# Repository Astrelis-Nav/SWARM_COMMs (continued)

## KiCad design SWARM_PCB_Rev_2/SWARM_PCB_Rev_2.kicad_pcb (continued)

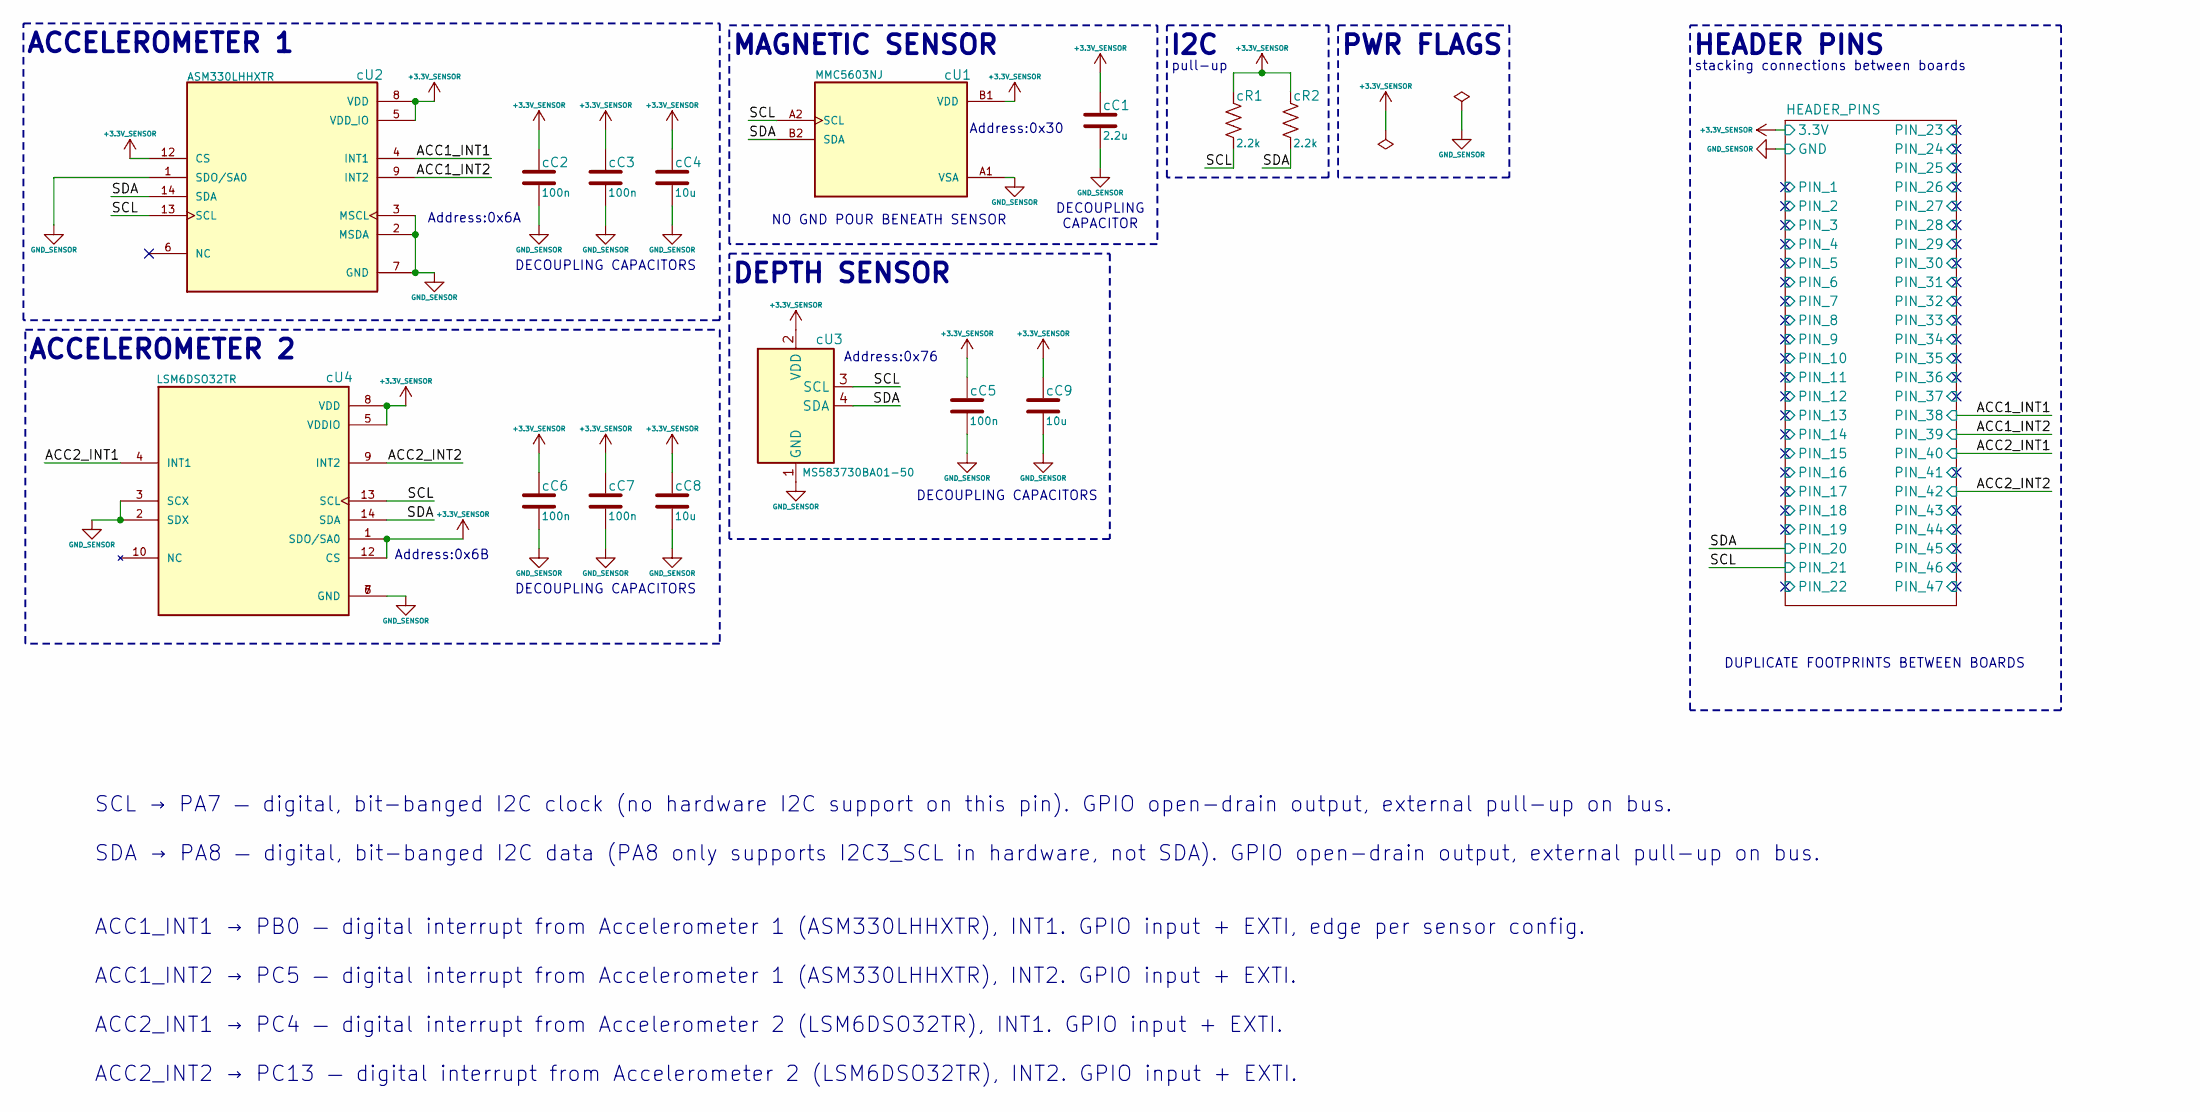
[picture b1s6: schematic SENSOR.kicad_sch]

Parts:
cC1: 2.2u; C_0603_1608Metric; MPN GRM188R60J225KE15D
cC2, cC3, cC5, cC6, cC7: 100n; C_0603_1608Metric; MPN GRM188R71C104KA01D
cC4, cC8, cC9: 10u; C_0603_1608Metric; MPN GRM188R60J106ME47D
cR1, cR2: 2.2k; R_0603_1608Metric; MPN RC0603FR-072K2L
cU1: MMC5603NJ; XDCR_MMC5603NJ; PARTREV B
cU2: ASM330LHHXTR; XDCR_ASM330LHHXTR; PARTREV 8
cU3: MS583730BA01-50; TE_MS5837-xxBA; MPN MS583730BA01-50
cU4: LSM6DSO32TR; XDCR_LSM6DSO32TR; PARTREV 1

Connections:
+3.3V_SENSOR: cC1.2, cC2.2, cC3.2, cC4.2, cC5.2, cC6.2, cC7.2, cC8.2, cC9.2, cR1.2, cR2.2, cU1.B1 (VDD), cU2.5 (VDD_IO), cU2.8 (VDD), cU2.12 (CS), cU3.2 (VDD), cU4.1 (SDO/SA0), cU4.5 (VDDIO), cU4.8 (VDD), cU4.12 (CS); also elsewhere on the board
/SENSOR/ACC1_INT1: cU2.4 (INT1); also elsewhere on the board
/SENSOR/ACC1_INT2: cU2.9 (INT2); also elsewhere on the board
/SENSOR/ACC2_INT1: cU4.4 (INT1); also elsewhere on the board
/SENSOR/ACC2_INT2: cU4.9 (INT2); also elsewhere on the board
/SENSOR/SCL: cR1.1, cU1.A2 (SCL), cU2.13 (SCL), cU3.3 (SCL), cU4.13 (SCL); also elsewhere on the board
/SENSOR/SDA: cR2.1, cU1.B2 (SDA), cU2.14 (SDA), cU3.4 (SDA), cU4.14 (SDA); also elsewhere on the board
GND_SENSOR: cC1.1, cC2.1, cC3.1, cC4.1, cC5.1, cC6.1, cC7.1, cC8.1, cC9.1, cU1.A1 (VSA), cU2.1 (SDO/SA0), cU2.2 (MSDA), cU2.3 (MSCL), cU2.7 (GND), cU3.1 (GND), cU4.2 (SDX), cU4.3 (SCX), cU4.6 (GND), cU4.7 (GND); also elsewhere on the board

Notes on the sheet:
Address:0x76
DECOUPLING CAPACITOR
DEPTH SENSOR
stacking connections between boards
MAGNETIC SENSOR
Address:0x6A
SCL → PA7 — digital, bit-banged I2C clock (no hardware I2C support on this pin). GPIO open-drain output, external pull-up on bus. SDA → PA8 — digital, bit-banged I2C data (PA8 only supports I2C3_SCL in hardware, not SDA). GPIO open-drain output, external pull-up on bus. ACC1_INT1 → PB0 — digital in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
DUPLICATE FOOTPRINTS BETWEEN BOARDS
DECOUPLING CAPACITORS
pull-up
Address:0x6B
ACCELEROMETER 2
Address:0x30
I2C
NO GND POUR BENEATH SENSOR
DECOUPLING CAPACITORS
PWR FLAGS
ACCELEROMETER 1
HEADER PINS

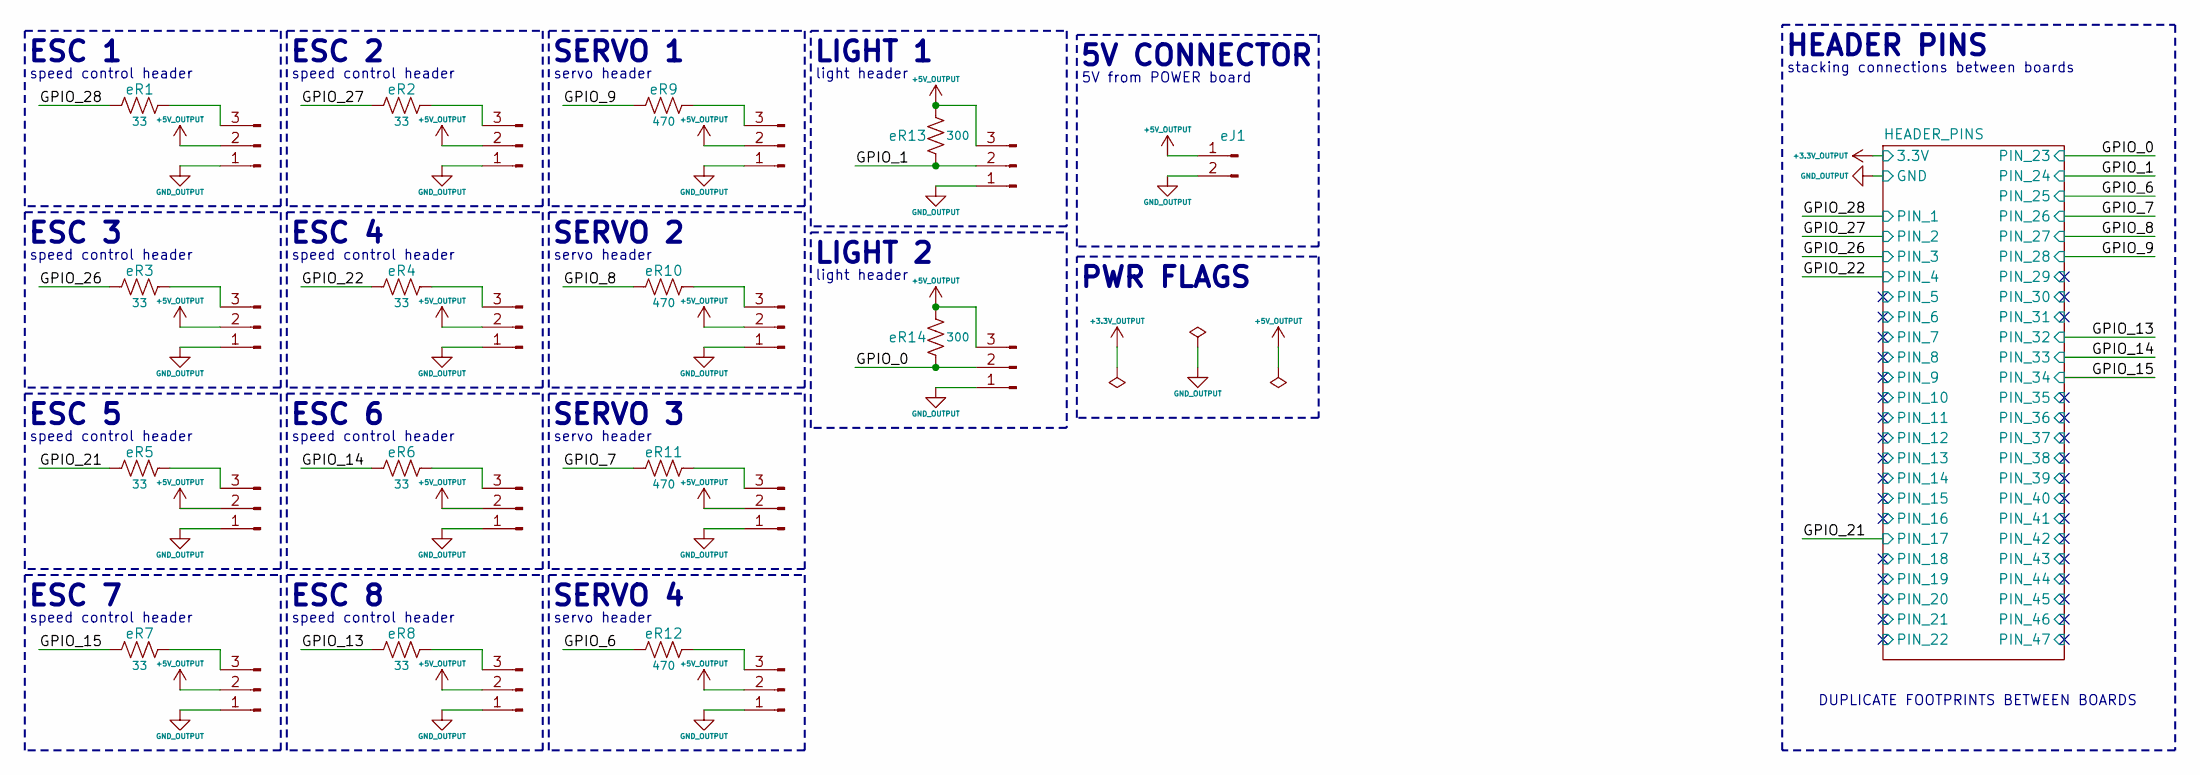
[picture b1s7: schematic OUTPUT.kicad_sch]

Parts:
OUT_1, OUT_2, OUT_3, OUT_4, OUT_5, OUT_6, OUT_7, OUT_8, OUT_9, OUT_10, OUT_11, OUT_12, OUT_13, OUT_14: Conn_01x03_Pin; PinHeader_1x03_P2.54mm_Vertical
eJ1: Conn_01x02_Pin; JST_PH_B2B-PH-SM4-TB_1x02-1MP_P2.00mm_Vertical
eR1, eR2, eR3, eR4, eR5, eR6, eR7, eR8: 33; R_0603_1608Metric
eR9, eR10, eR11, eR12: 470; R_0603_1608Metric
eR13, eR14: 300; R_0603_1608Metric

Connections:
+5V_OUTPUT: OUT_1.2, OUT_2.2, OUT_3.2, OUT_4.2, OUT_5.2, OUT_6.2, OUT_7.2, OUT_8.2, OUT_9.2, OUT_10.2, OUT_11.2, OUT_12.2, OUT_13.3, OUT_14.3, eJ1.1, eR13.2, eR14.2
/OUTPUT/GPIO_0: OUT_14.2, eR14.1; also elsewhere on the board
/OUTPUT/GPIO_1: OUT_13.2, eR13.1; also elsewhere on the board
/OUTPUT/GPIO_6: eR12.1; also elsewhere on the board
/OUTPUT/GPIO_7: eR11.1; also elsewhere on the board
/OUTPUT/GPIO_8: eR10.1; also elsewhere on the board
/OUTPUT/GPIO_9: eR9.1; also elsewhere on the board
/OUTPUT/GPIO_13: eR8.1; also elsewhere on the board
/OUTPUT/GPIO_14: eR6.1; also elsewhere on the board
/OUTPUT/GPIO_15: eR7.1; also elsewhere on the board
/OUTPUT/GPIO_21: eR5.1; also elsewhere on the board
/OUTPUT/GPIO_22: eR4.1; also elsewhere on the board
/OUTPUT/GPIO_26: eR3.1; also elsewhere on the board
/OUTPUT/GPIO_27: eR2.1; also elsewhere on the board
/OUTPUT/GPIO_28: eR1.1; also elsewhere on the board
GND_OUTPUT: OUT_1.1, OUT_2.1, OUT_3.1, OUT_4.1, OUT_5.1, OUT_6.1, OUT_7.1, OUT_8.1, OUT_9.1, OUT_10.1, OUT_11.1, OUT_12.1, OUT_13.1, OUT_14.1, eJ1.2; also elsewhere on the board
unnamed: OUT_1.3, eR1.2
unnamed: OUT_2.3, eR2.2
unnamed: OUT_3.3, eR3.2
unnamed: OUT_4.3, eR4.2
unnamed: OUT_5.3, eR5.2
unnamed: OUT_6.3, eR6.2
unnamed: OUT_7.3, eR7.2
unnamed: OUT_8.3, eR8.2
unnamed: OUT_9.3, eR9.2
unnamed: OUT_10.3, eR10.2
unnamed: OUT_11.3, eR11.2
unnamed: OUT_12.3, eR12.2

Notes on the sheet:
servo header
ESC 1
SERVO 1
ESC 8
ESC 3
ESC 5
SERVO 2
speed control header
PWR FLAGS
SERVO 4
ESC 4
light header
DUPLICATE FOOTPRINTS BETWEEN BOARDS
ESC 7
ESC 6
LIGHT 2
5V from POWER board
5V CONNECTOR
LIGHT 1
HEADER PINS
stacking connections between boards
ESC 2
SERVO 3

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
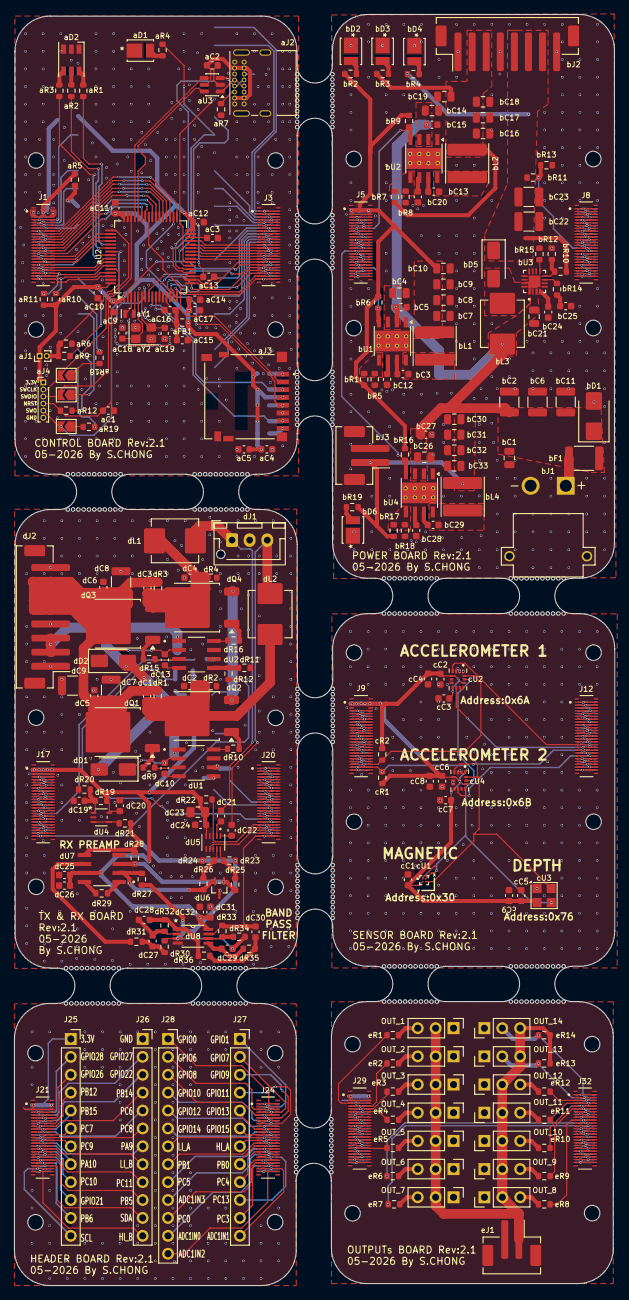
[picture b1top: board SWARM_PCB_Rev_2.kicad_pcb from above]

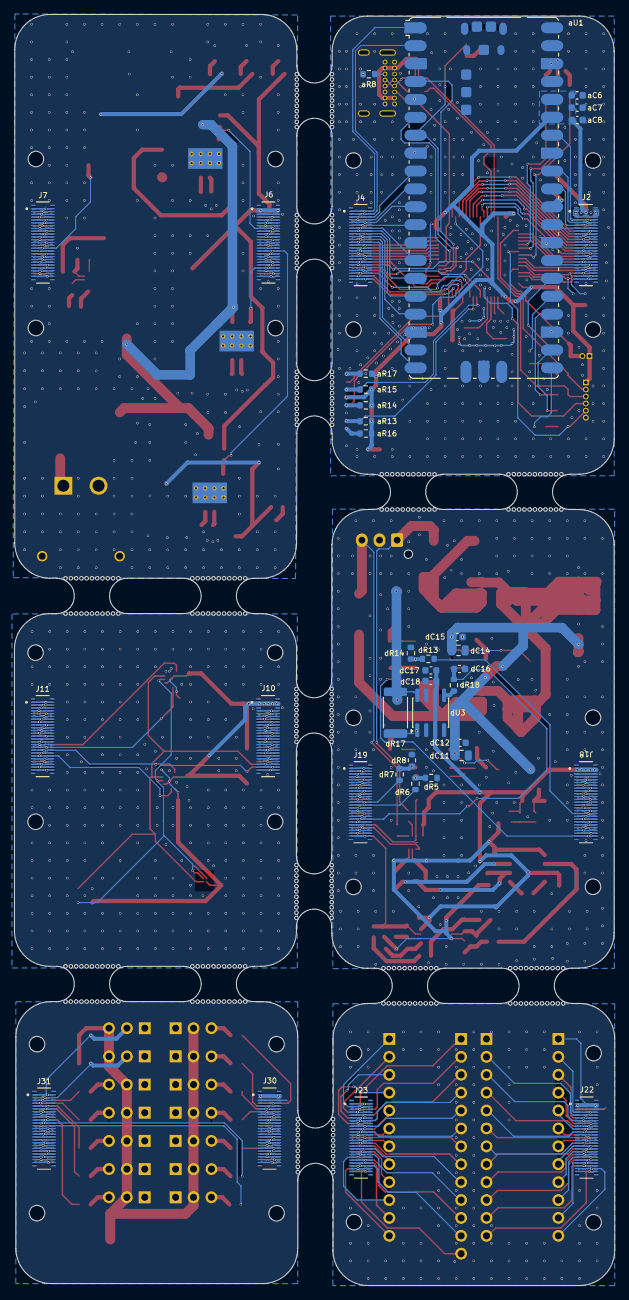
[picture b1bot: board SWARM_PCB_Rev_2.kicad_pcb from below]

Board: 2 copper layers, 85.2 x 180.4 mm, 295 parts (38 on the bottom side), 419 nets.

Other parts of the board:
mouse-bite-5mm-slot, mouse-bite-5mm-slot#2, mouse-bite-5mm-slot#3, mouse-bite-5mm-slot#4, mouse-bite-5mm-slot#5, mouse-bite-5mm-slot#6, mouse-bite-5mm-slot#7, mouse-bite-5mm-slot#8, mouse-bite-5mm-slot#9, mouse-bite-5mm-slot#10, mouse-bite-5mm-slot#11, mouse-bite-5mm-slot#12, mouse-bite-5mm-slot#13, mouse-bite-5mm-slot#14: VAL**; mouse-bite-5mm-slot

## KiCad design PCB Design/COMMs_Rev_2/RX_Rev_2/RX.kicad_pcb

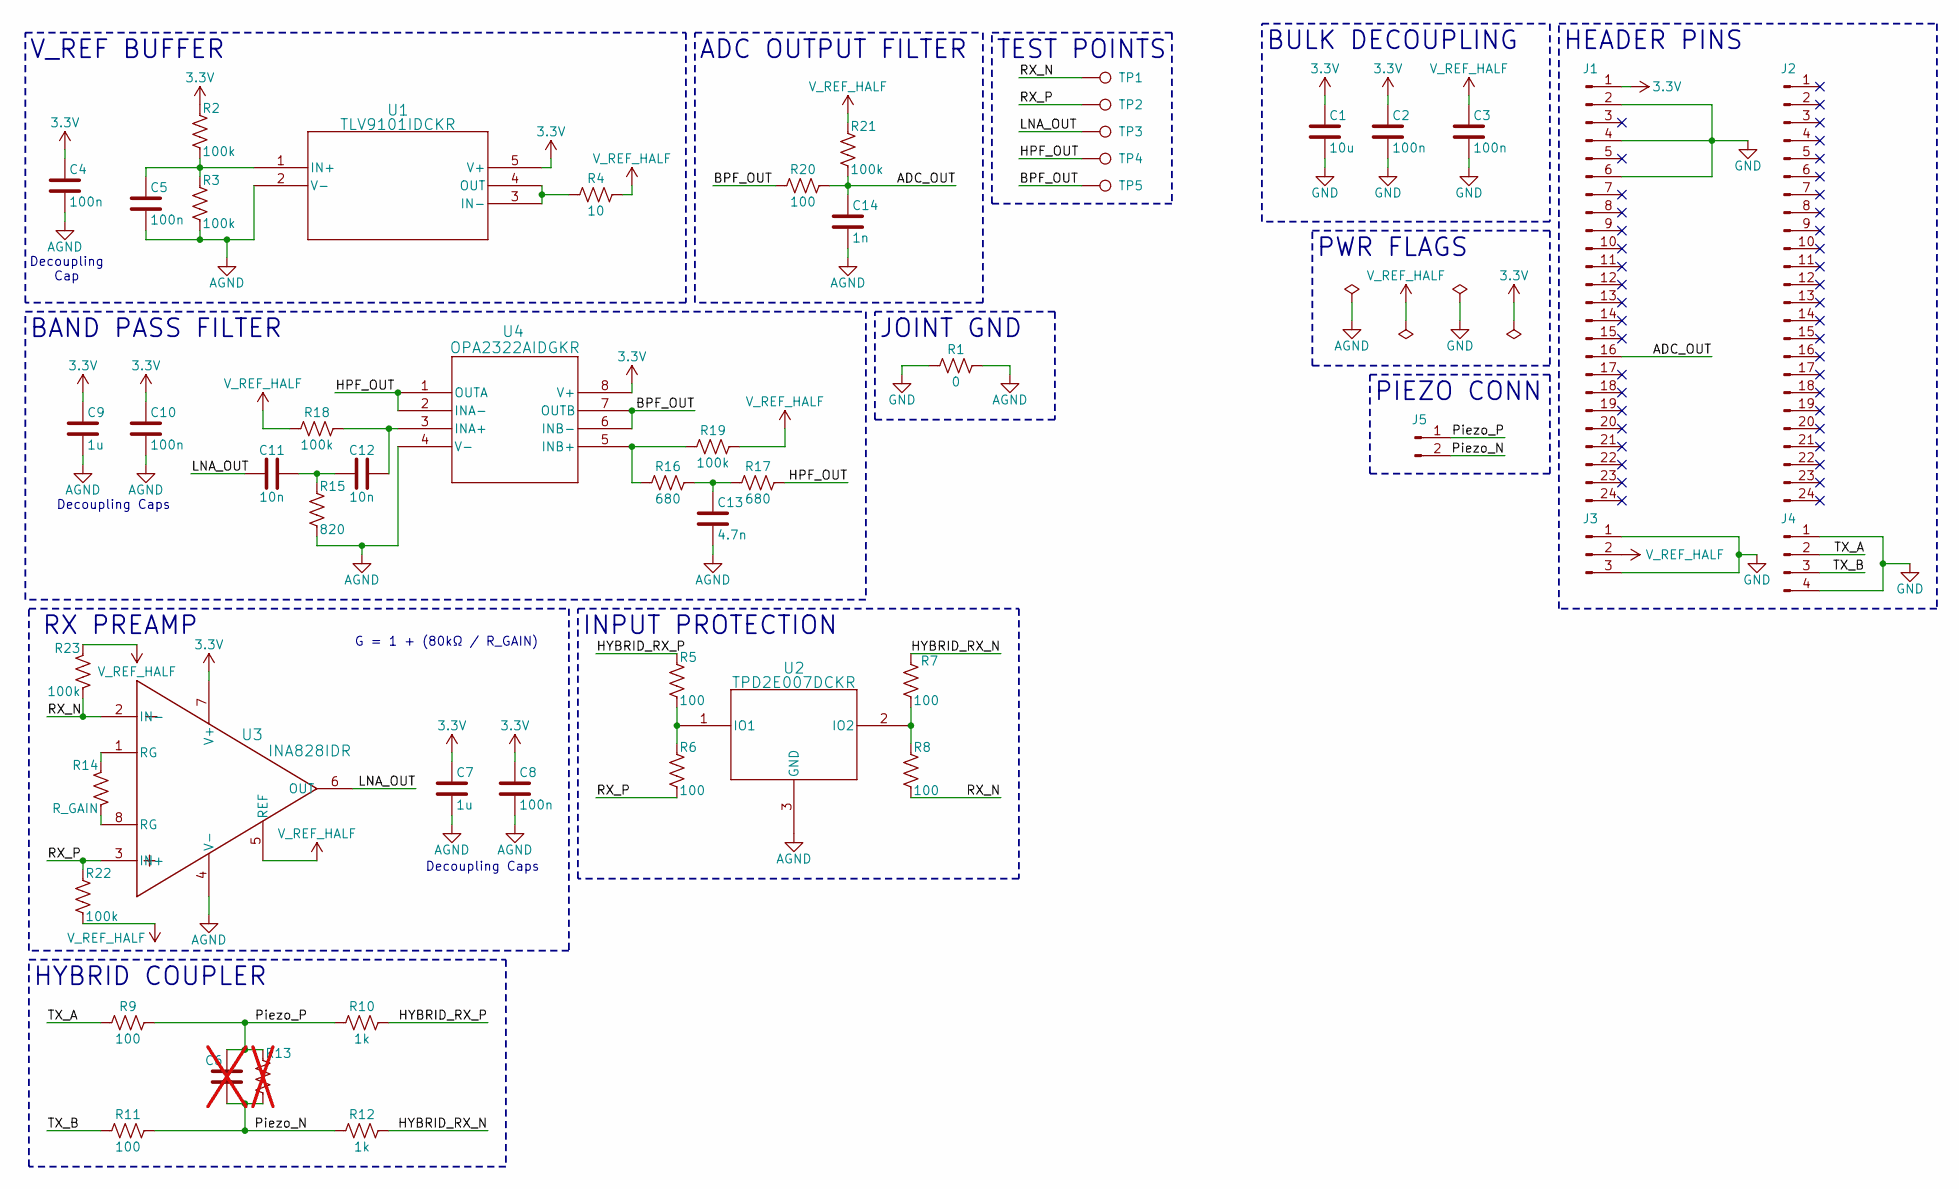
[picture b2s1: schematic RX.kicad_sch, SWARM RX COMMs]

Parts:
C1: 10u; C_1206_3216Metric
C2, C3, C4, C5, C8, C10: 100n; C_0603_1608Metric
C6: C_0603_1608Metric; not fitted
C7, C9: 1u; C_0603_1608Metric
C11, C12: 10n; C_0603_1608Metric
C13: 4.7n; C_0603_1608Metric
C14: 1n; C_0603_1608Metric
J1, J2: Conn_01x24_Pin; PinHeader_1x24_P2.54mm_Vertical
J3: Conn_01x03_Pin; PinHeader_1x03_P2.54mm_Vertical
J4: Conn_01x04_Pin; PinHeader_1x04_P2.54mm_Vertical
J5: Conn_01x02_Pin; JST_VH_B2P-VH_1x02_P3.96mm_Vertical
R1: 0; R_0603_1608Metric
R2, R3, R18, R19, R21, R22, R23: 100k; R_0603_1608Metric
R4: 10; R_0603_1608Metric
R5, R6, R7, R8, R9, R11, R20: 100; R_0603_1608Metric
R10, R12: 1k; R_0603_1608Metric
R13: R_0603_1608Metric; not fitted
R14: R_GAIN; R_0603_1608Metric
R15: 820; R_0603_1608Metric
R16, R17: 680; R_0603_1608Metric
TP1, TP2, TP3, TP4, TP5: TestPoint; TestPoint_Pad_1.0x1.0mm
U1: TLV9101IDCKR; SC70-5_DCK_TEX
U2: TPD2E007DCKR; DCK3
U3: INA828IDR; D0008A_L
U4: OPA2322AIDGKR; DGK8

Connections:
3.3V: C1.1, C2.1, C4.1, C7.1, C8.1, C9.1, C10.1, J1.1, R2.1, U1.5 (V+), U3.7 (V+), U4.8 (V+)
/ADC_OUT: C14.1, J1.16, R20.2, R21.2
/BPF_OUT: R20.1, TP5.1, U4.6 (INB-), U4.7 (OUTB)
/HPF_OUT: R17.2, TP4.1, U4.1 (OUTA), U4.2 (INA-)
/HYBRID_RX_N: R7.1, R12.2
/HYBRID_RX_P: R5.1, R10.2
/LNA_OUT: C11.1, TP3.1, U3.6 (OUT)
/Piezo_N: C6.2, J5.2, R11.2, R12.1, R13.2
/Piezo_P: C6.1, J5.1, R9.2, R10.1, R13.1
/RX_N: R8.2, R23.2, TP1.1, U3.2 (IN-)
/RX_P: R6.2, R22.1, TP2.1, U3.3 (IN+)
/TX_A: J4.2, R9.1
/TX_B: J4.3, R11.1
GND: C1.2, C2.2, C3.2, J1.2, J1.4, J1.6, J3.1, J3.3, J4.1, J4.4, R1.1
unnamed: C11.2, C12.1, R15.1
unnamed: C13.1, R16.2, R17.1
unnamed: R14.1, U3.1 (RG)
unnamed: R14.2, U3.8 (RG)
unnamed: C5.1, R2.2, R3.1, U1.1 (IN+)
unnamed: R4.1, U1.3 (IN-), U1.4 (OUT)
unnamed: R5.2, R6.1, U2.1 (IO1)
unnamed: R7.2, R8.1, U2.2 (IO2)
unnamed: C12.2, R18.2, U4.3 (INA+)
unnamed: R16.1, R19.1, U4.5 (INB+)

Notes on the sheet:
RX PREAMP
ADC OUTPUT FILTER
V_REF BUFFER
HYBRID COUPLER
Decoupling Caps
G = 1 + (80kΩ / R_GAIN)
TEST POINTS
JOINT GND
BAND PASS FILTER
INPUT PROTECTION
PIEZO CONN
BULK DECOUPLING
Decoupling Cap
PWR FLAGS
HEADER PINS

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
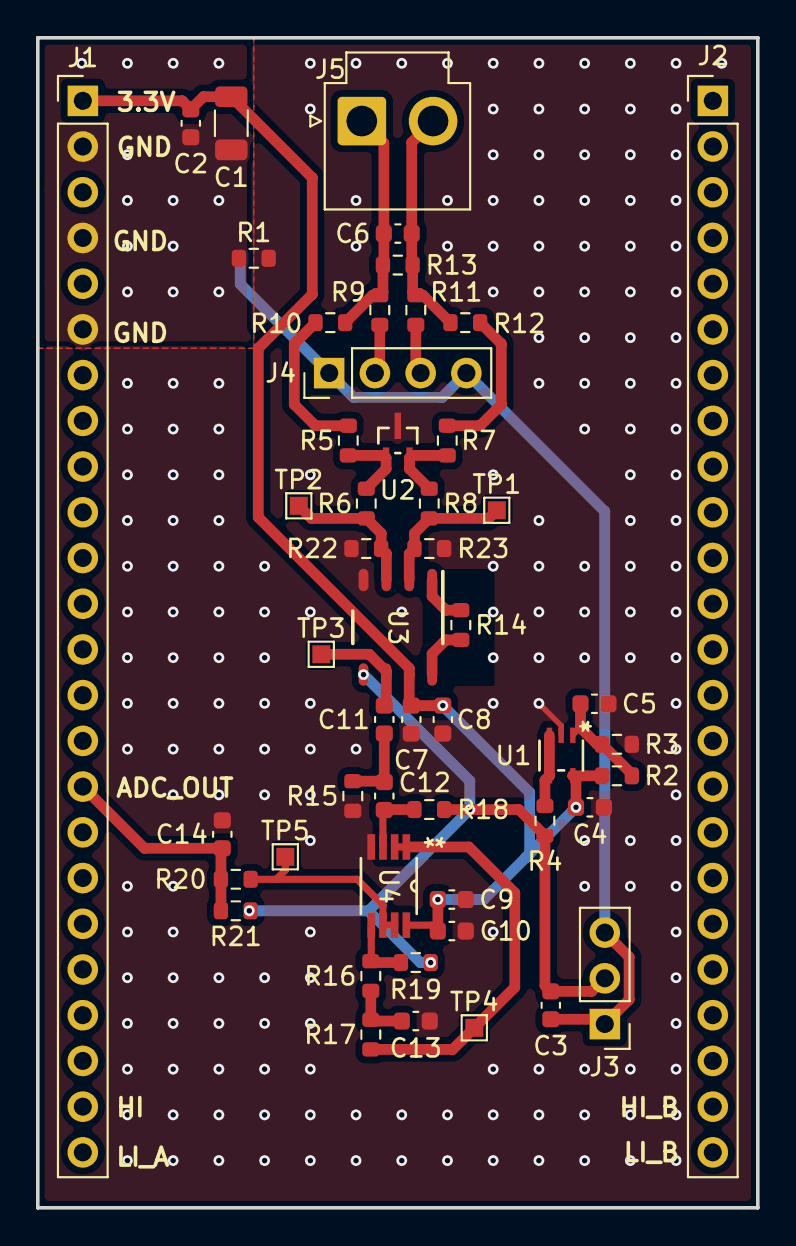
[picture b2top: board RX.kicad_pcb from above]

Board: 2 copper layers, 40.0 x 65.0 mm, 51 parts (0 on the bottom side), 26 nets.

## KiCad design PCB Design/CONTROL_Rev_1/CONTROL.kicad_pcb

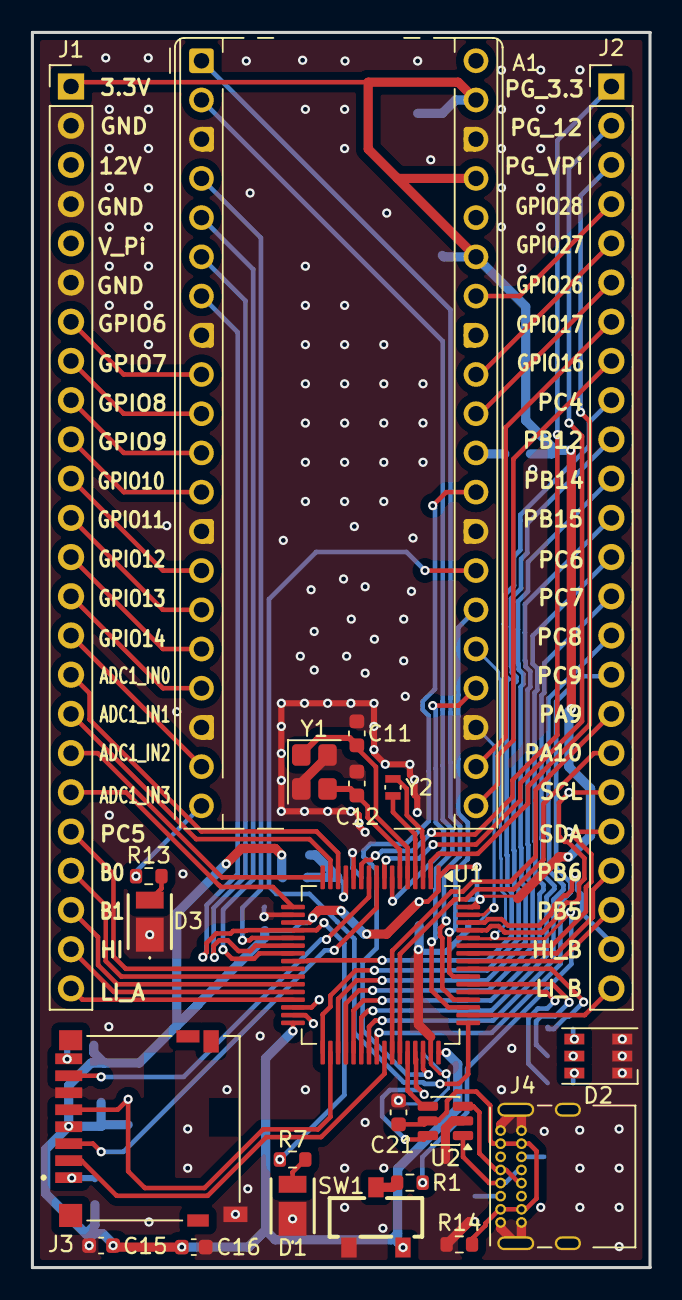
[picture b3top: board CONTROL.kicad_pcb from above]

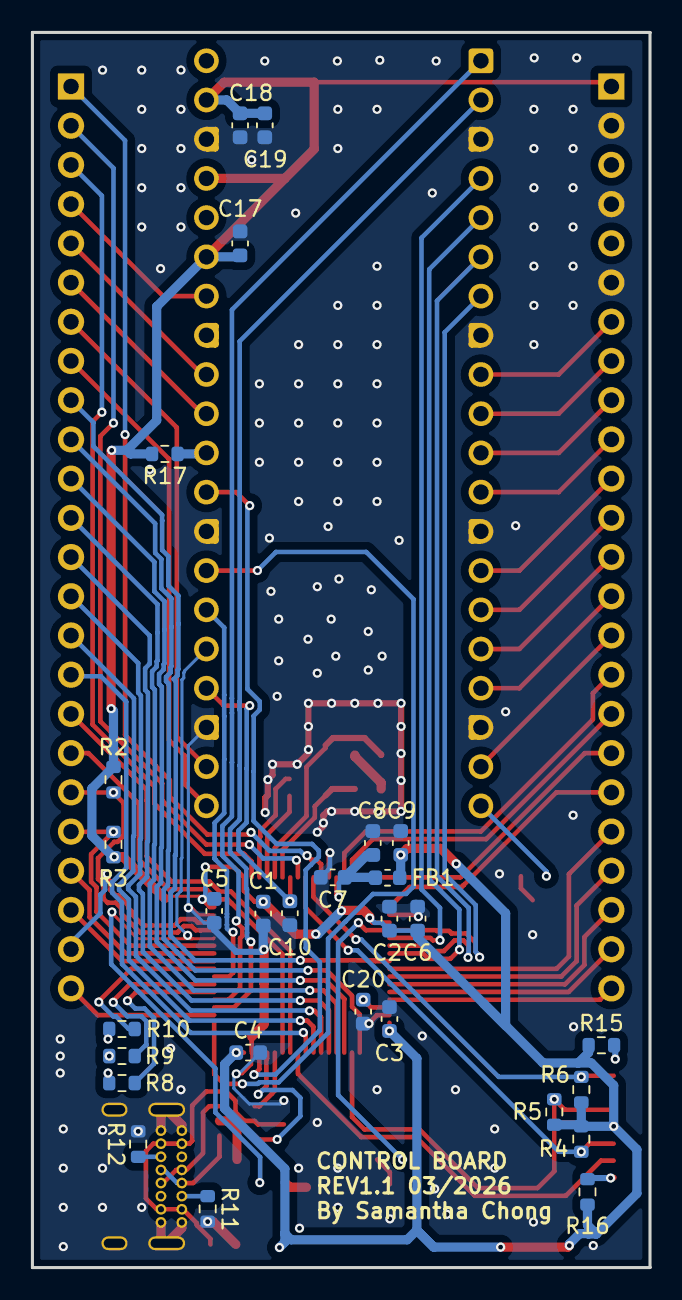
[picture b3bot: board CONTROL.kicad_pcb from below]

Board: 2 copper layers, 40.0 x 80.0 mm, 50 parts (28 on the bottom side), 85 nets.

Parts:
A1: RaspberryPi_Pico; RaspberryPi_Pico_Common_THT
C1, C2, C3, C4, C5, C10, C17, C18, C21: 100n; C_0603_1608Metric
C6, C16, C19: 10u; C_0603_1608Metric
C7: 10n; C_0603_1608Metric
C8, C9: 1u; C_0603_1608Metric
C11, C12: 10p; C_0603_1608Metric
C15: 0.1u; C_0603_1608Metric
C20: 2.2u; C_0603_1608Metric
D1: PURPLE; JB2835AWTWU57EA0000N0000001
D2: LED_RGB; LED_RGB_PLCC-6
D3: MINT; JB2835AWTWU57EA0000N0000001
FB1: 120R; L_0603_1608Metric
J1, J2: Conn_01x24_Pin; PinHeader_1x24_P2.54mm_Vertical
J3: Micro_SD_Card; AMPHENOL_1140084168
J4: USB_C_Receptacle_USB2.0_16P; USB_C_Receptacle_GCT_USB4085
R1, R4, R5, R6, R17: 10k; R_0603_1608Metric
R2, R3: 4.7k; R_0603_1608Metric
R7, R8, R9, R10, R13: 1k; R_0603_1608Metric
R11, R12: 5.1k; R_0603_1608Metric
R14: 100k; R_0603_1608Metric
R15, R16: 47k; R_0603_1608Metric
SW1: SW_SPDT; B-TYPE
U1: STM32F446RET6; LQFP-64_10x10mm_P0.5mm
U2: USBLC6-2SC6; SOT-23-6
Y1: 16MHz; Crystal_SMD_3225-4Pin_3.2x2.5mm
Y2: 32.768KHz; XTAL_ABS05W-32.768KHZ-D-2-T

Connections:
3.3V: A1.35 (ADC_VREF), A1.37 (3V3_EN), A1.39 (VSYS), C1.1, C2.1, C3.1, C4.1, C5.1, C6.1, C9.1, C15.1, C16.1, C17.1, C18.1, C19.1, FB1.2, J1.1, J3.4 (VDD), R2.1, R3.1, R4.1, R5.1, R6.1, R15.1, R16.1, R17.2, SW1.3 (C), U1.1 (VBAT), U1.19 (VDD), U1.32 (VDD), U1.48 (VDD), U1.64 (VDD)
3.3VA: C7.1, C8.1, FB1.1, U1.13 (VDDA)
/ADC1_IN0: J1.16, U1.14 (PA0)
/ADC1_IN1: J1.17, U1.15 (PA1)
/ADC1_IN2: J1.18, U1.16 (PA2)
/ADC1_IN3: J1.19, U1.17 (PA3)
/BOOT0: A1.25 (GPIO19), R1.2, U1.60 (BOOT0)
/CS: J3.2 (DAT3/CD), U1.41 (PA8)
/DAT1: J3.8 (DAT1), R15.2
/DAT2: J3.1 (DAT2), R16.2
/GPIO_6: A1.9 (GPIO6), J1.7
/GPIO_7: A1.10 (GPIO7), J1.8
/GPIO_8: A1.11 (GPIO8), J1.9
/GPIO_9: A1.12 (GPIO9), J1.10
/GPIO_10: A1.14 (GPIO10), J1.11
/GPIO_11: A1.15 (GPIO11), J1.12
/GPIO_12: A1.16 (GPIO12), J1.13
/GPIO_13: A1.17 (GPIO13), J1.14
/GPIO_14: A1.19 (GPIO14), J1.15
/GPIO_15: A1.20 (GPIO15), R13.2
/GPIO_16: A1.21 (GPIO16), J2.8
/GPIO_17: A1.22 (GPIO17), J2.7
/GPIO_26: A1.31 (GPIO26_ADC0), J2.6
/GPIO_27: A1.32 (GPIO27_ADC1), J2.5
/GPIO_28: A1.34 (GPIO28_ADC2), J2.4
/HEARTBEAT: A1.7 (GPIO5), R7.2, U1.20 (PA4)
/HI_A: J1.23, U1.28 (PB2)
/HI_B: J2.23, U1.62 (PB9)
/HSE_IN: C11.1, U1.5 (PH0), Y1.1
/HSE_OUT: C12.1, U1.6 (PH1), Y1.3
/LED_BLUE: R10.2, U1.56 (PB4)
/LED_GREEN: R9.2, U1.54 (PD2)
/LED_RED: R8.2, U1.53 (PC12)
/LI_A: J1.24, U1.29 (PB10)
/LI_B: J2.24, U1.50 (PA15)
/LSE_IN: U1.3 (PC14), Y2.1
/LSE_OUT: U1.4 (PC15), Y2.2
/NRST: A1.24 (GPIO18), C10.2, U1.7 (NRST)
/PA9: J2.17, U1.42 (PA9)
/PA10: J2.18, U1.43 (PA10)
/PB0: J1.21, U1.26 (PB0)
/PB1: J1.22, U1.27 (PB1)
/PB5: J2.22, U1.57 (PB5)
/PB6: J2.21, U1.58 (PB6)
/PB12: J2.10, U1.33 (PB12)
/PB14: J2.11, U1.35 (PB14)
/PB15: J2.12, U1.36 (PB15)
/PC0: J2.2, U1.8 (PC0)
/PC3: J2.1, U1.11 (PC3)
/PC4: J2.9, U1.24 (PC4)
/PC5: J1.20, U1.25 (PC5)
/PC6: J2.13, U1.37 (PC6)
/PC7: J2.14, U1.38 (PC7)
/PC8: J2.15, U1.39 (PC8)
/PC9: J2.16, U1.40 (PC9)
/PC13: J2.3, U1.2 (PC13)
/SCL: J2.19, R2.2, U1.61 (PB8)
/SDA: J2.20, R3.2, U1.59 (PB7)
/SPI2_MISO: J3.7 (DAT0), R6.2, U1.10 (PC2)
/SPI2_MOSI: J3.3 (CMD), R4.2, U1.9 (PC1)
/SPI2_SCK: J3.5 (CLK), R5.2, U1.34 (PB13)
/SPI_MISO: A1.6 (GPIO4), U1.22 (PA6)
/SPI_MOSI: A1.5 (GPIO3), U1.23 (PA7)
/SPI_SCK: A1.4 (GPIO2), U1.21 (PA5)
/STM_UART_RX: A1.1 (GPIO0), U1.52 (PC11)
/STM_UART_TX: A1.2 (GPIO1), U1.51 (PC10)
/SWCLK: A1.27 (GPIO21), U1.49 (PA14)
/SWDIO: A1.29 (GPIO22), U1.46 (PA13)
/SWO: A1.26 (GPIO20), U1.55 (PB3)
/USB_D+: U1.45 (PA12), U2.6 (I/O1)
/USB_D+IN: J4.A6 (D+), J4.B6 (D+), U2.1 (I/O1)
/USB_D-: U1.44 (PA11), U2.4 (I/O2)
/USB_D-IN: J4.A7 (D-), J4.B7 (D-), U2.3 (I/O2)
GND: A1.3 (GND), A1.8 (GND), A1.13 (GND), A1.18 (GND), A1.23 (GND), A1.28 (GND), A1.38 (GND), C1.2, C2.2, C3.2, C4.2, C5.2, C6.2, C7.2, C8.2, C9.2, C10.1, C11.2, C12.2, C15.2, C16.2, C17.2, C18.2, C19.2, C20.1, C21.2, D1.1 (K), D2.1 (RK), D2.2 (GK), D2.3 (BK), D3.1 (K), J1.2, J1.4, J1.6, J3.6 (VSS), J3.9 (SHIELD), J4.A1 (GND), J4.A12 (GND), J4.B1 (GND), J4.B12 (GND), J4.S1 (SHIELD), R11.2, R12.2, R14.2, SW1.1 (A), U1.12 (VSSA), U1.18 (VSS), U1.31 (VSS), U1.47 (VSS), U1.63 (VSS), U2.2 (GND), Y1.2, Y1.4
unnamed: A1.30 (RUN), R17.1
unnamed: D1.2 (A), R7.1
unnamed: D2.4 (BA), R10.1
unnamed: D2.5 (GA), R9.1
unnamed: D2.6 (RA), R8.1
unnamed: D3.2 (A), R13.1
unnamed: J4.A5 (CC1), R11.1
unnamed: J4.B5 (CC2), R12.1
unnamed: R1.1, SW1.2 (B)
unnamed: C20.2, U1.30 (VCAP_1)
VBUS: C21.1, J4.A4 (VBUS), J4.A9 (VBUS), J4.B4 (VBUS), J4.B9 (VBUS), R14.1, U2.5 (VBUS)
